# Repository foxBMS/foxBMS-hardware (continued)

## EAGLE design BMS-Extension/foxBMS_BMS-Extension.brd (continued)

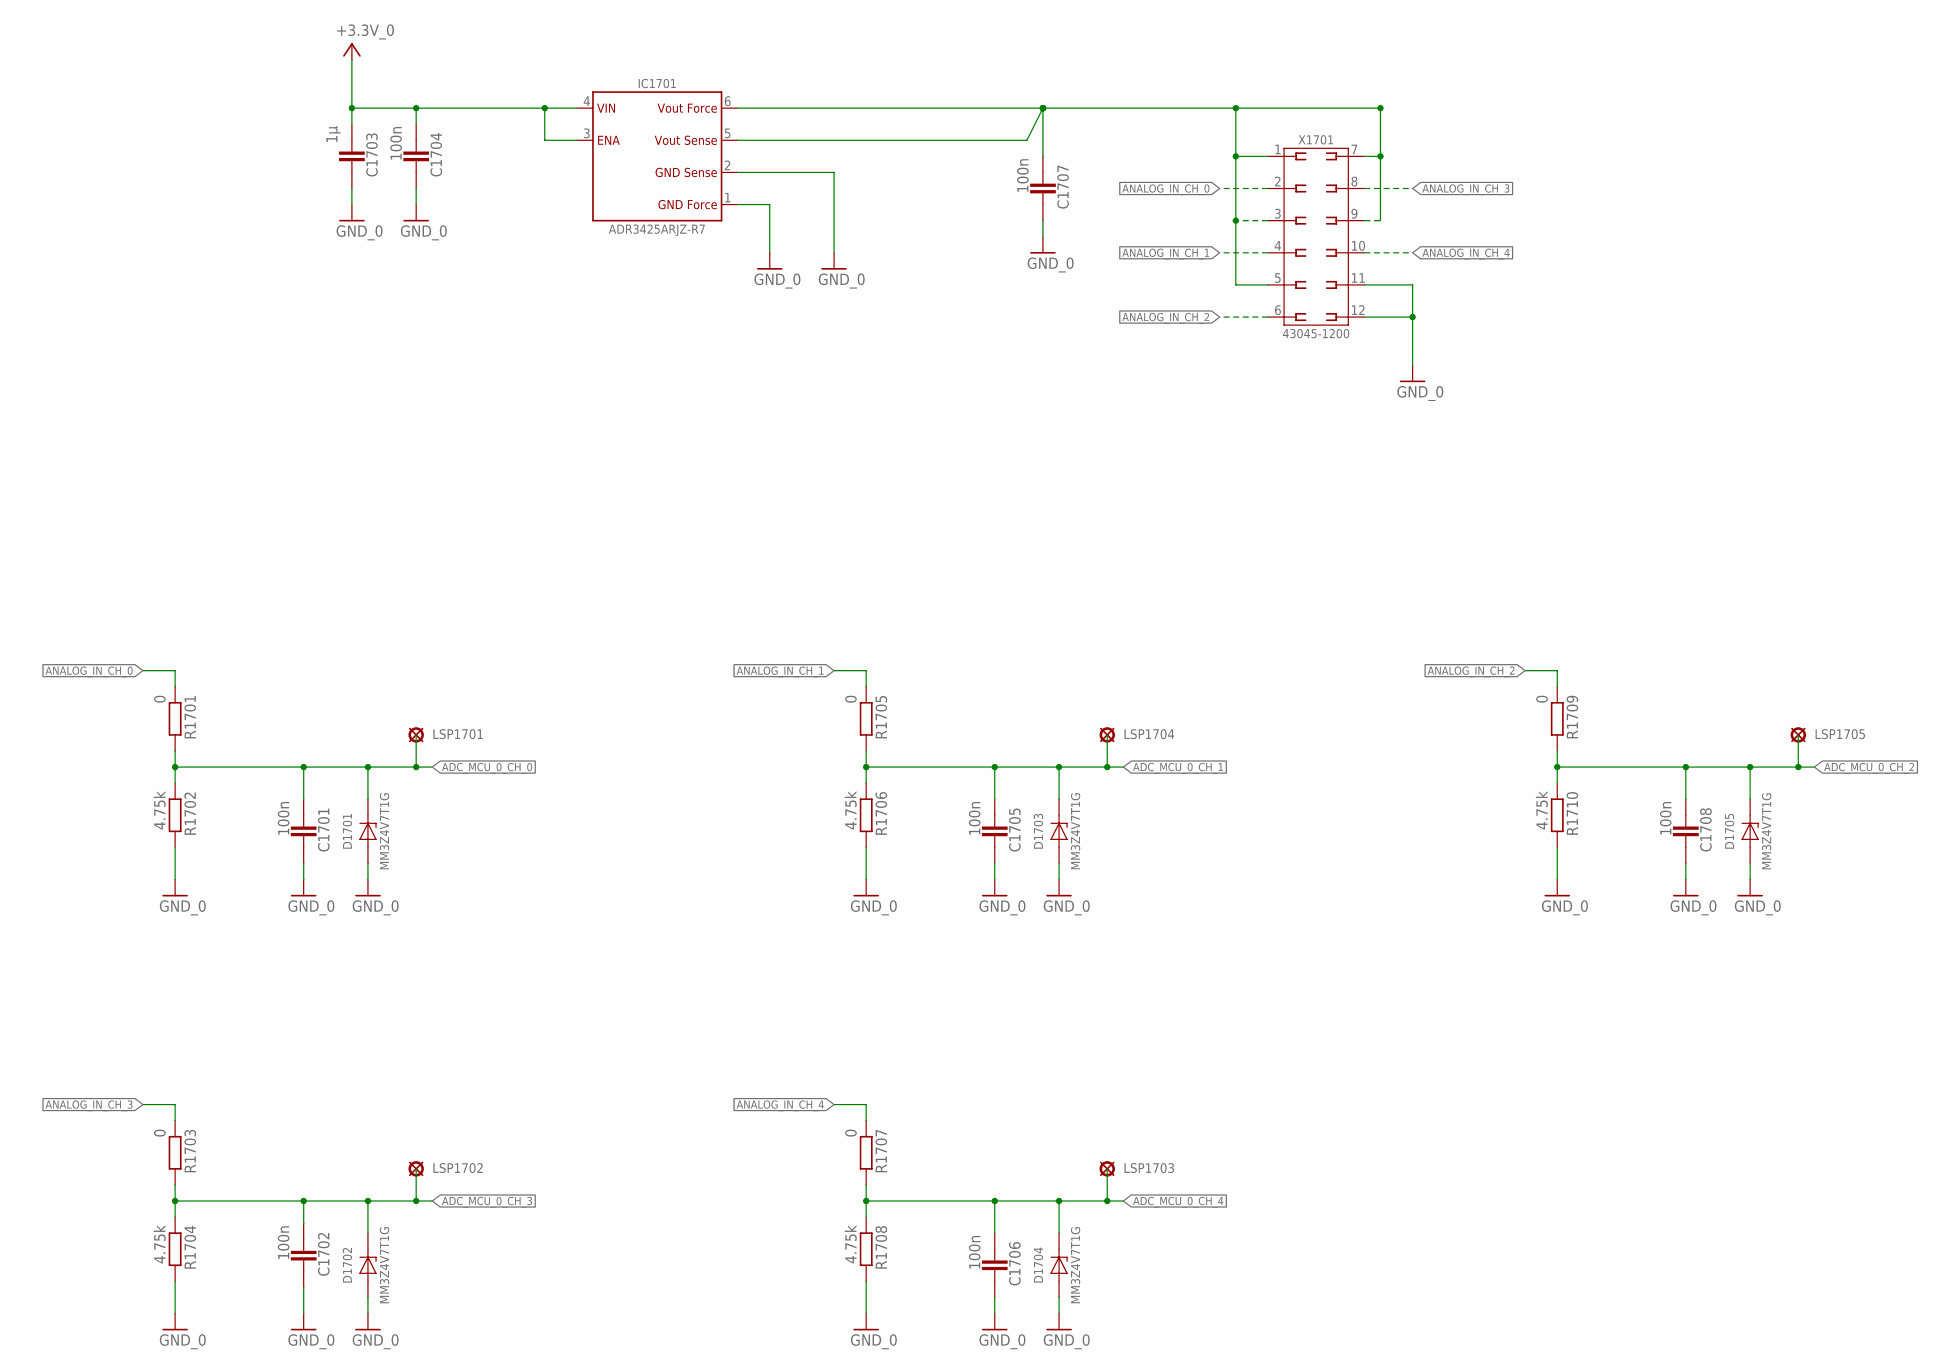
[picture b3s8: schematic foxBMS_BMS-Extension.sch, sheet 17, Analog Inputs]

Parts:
C1701, C1702, C1704, C1705, C1706, C1707, C1708: 100n; 0603
C1703: 1µ; 0603
D1701, D1702, D1703, D1704, D1705: MM3Z3V3ST1G; D_SMD_SOD323_(SC-76)_R_ON_REV01
IC1701: ADR3425ARJZ; IC_SMD_SOT23-6_(MO-178-AB)_R_AD_REV01
LSP1701, LSP1702, LSP1703, LSP1704, LSP1705: PAD_2.0X1.5MM; PAD2.0X1.5MM
R1701, R1703, R1705, R1707, R1709: 0; 0603
R1702, R1704, R1706, R1708, R1710: 4.75k; 0603
X1701: 43045-1200_MOLEX_12PIN; X_TH_MOLEX_43045-1200_R_REV01

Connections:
+3.3V_0: C1703.1, C1704.1, IC1701.3 (ENABLE), IC1701.4 (VIN); also elsewhere on the board
ADC_MCU_0_CH_0: C1701.1, D1701.C, LSP1701.P$1, R1701.2, R1702.1; also elsewhere on the board
ADC_MCU_0_CH_1: C1705.1, D1703.C, LSP1704.P$1, R1705.2, R1706.1; also elsewhere on the board
ADC_MCU_0_CH_2: C1708.1, D1705.C, LSP1705.P$1, R1709.2, R1710.1; also elsewhere on the board
ADC_MCU_0_CH_3: C1702.1, D1702.C, LSP1702.P$1, R1703.2, R1704.1; also elsewhere on the board
ADC_MCU_0_CH_4: C1706.1, D1704.C, LSP1703.P$1, R1707.2, R1708.1; also elsewhere on the board
ANALOG_IN_CH_0: R1701.1, X1701.2
ANALOG_IN_CH_1: R1705.1, X1701.4
ANALOG_IN_CH_2: R1709.1, X1701.6
ANALOG_IN_CH_3: R1703.1, X1701.8
ANALOG_IN_CH_4: R1707.1, X1701.10
GND_0: C1701.2, C1702.2, C1703.2, C1704.2, C1705.2, C1706.2, C1707.2, C1708.2, D1701.A, D1702.A, D1703.A, D1704.A, D1705.A, IC1701.1 (GND_FORCE), IC1701.2 (GND_SENSE), R1702.2, R1704.2, R1706.2, R1708.2, R1710.2, X1701.11, X1701.12; also elsewhere on the board
unnamed: C1707.1, IC1701.5 (VOUT_SENSE), IC1701.6 (VOUT_FORCE), X1701.1, X1701.3, X1701.5, X1701.7, X1701.9

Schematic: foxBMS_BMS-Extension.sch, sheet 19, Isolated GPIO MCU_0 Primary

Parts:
C1901, C1903, C1904, C1905, C1906, C1907: 100n; 0603
C1902: 1µ; 0603
D1901, D1902, D1903, D1904: CDSOD323-T05; D_SMD_SOD323_(SC-76)_R_BOURNS_REV01
IC1901: UA78L05ACPK; IC_SMD_SOT-89_(SC-62/TO-243)_(R-PSSO-F3)_R_TI_REV01
IC1902, IC1903: ADUM1402ARW; IC_SMD_SOIC-16_(JEDEC_MS-013-AA)_R_ANALOG_REV01
LSP1901, LSP1902, LSP1903, LSP1904, LSP1905, LSP1906, LSP1907, LSP1908: PAD_2.0X1.5MM; PAD2.0X1.5MM
R1901, R1902, R1905, R1906: 47; 0603
R1903, R1904, R1907, R1908: 10k; 0603
X1901: 43045-1000_MOLEX_10PIN; X_TH_MOLEX_43045-1000_R_REV01

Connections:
+3.3V_0: C1905.1, C1907.1, IC1902.10 (VE2), IC1902.16 (VDD2), IC1903.10 (VE2), IC1903.16 (VDD2); also elsewhere on the board
GND_0: C1905.2, C1907.2, IC1902.9 (GND2), IC1902.15 (GND2), IC1903.9 (GND2), IC1903.15 (GND2); also elsewhere on the board
GND_EXT_0: C1901.2, C1902.2, C1903.2, C1904.2, C1906.2, D1901.A, D1902.A, D1903.A, D1904.A, IC1901.2 (COM), IC1902.2 (GND1), IC1902.8 (GND1), IC1903.2 (GND1), IC1903.8 (GND1), R1903.1, R1904.1, R1907.1, R1908.1, X1901.9, X1901.10; also elsewhere on the board
ISO_GPIO_MCU_0_IN_0: IC1902.14 (VOA), LSP1903.P$1; also elsewhere on the board
ISO_GPIO_MCU_0_IN_0_EXT: R1901.2, X1901.5
ISO_GPIO_MCU_0_IN_1: IC1902.13 (VOB), LSP1901.P$1; also elsewhere on the board
ISO_GPIO_MCU_0_IN_1_EXT: R1902.2, X1901.6
ISO_GPIO_MCU_0_IN_2: IC1903.14 (VOA), LSP1905.P$1; also elsewhere on the board
ISO_GPIO_MCU_0_IN_2_EXT: R1905.2, X1901.7
ISO_GPIO_MCU_0_IN_3: IC1903.13 (VOB), LSP1907.P$1; also elsewhere on the board
ISO_GPIO_MCU_0_IN_3_EXT: R1906.2, X1901.8
ISO_GPIO_MCU_0_OUT_0: IC1902.12 (VIC), LSP1904.P$1; also elsewhere on the board
ISO_GPIO_MCU_0_OUT_0_EXT: IC1902.5 (VOC), R1903.2, X1901.1
ISO_GPIO_MCU_0_OUT_1: IC1902.11 (VID), LSP1902.P$1; also elsewhere on the board
ISO_GPIO_MCU_0_OUT_1_EXT: IC1902.6 (VOD), R1904.2, X1901.2
ISO_GPIO_MCU_0_OUT_2: IC1903.12 (VIC), LSP1906.P$1; also elsewhere on the board
ISO_GPIO_MCU_0_OUT_2_EXT: IC1903.5 (VOC), R1907.2, X1901.3
ISO_GPIO_MCU_0_OUT_3: IC1903.11 (VID), LSP1908.P$1; also elsewhere on the board
ISO_GPIO_MCU_0_OUT_3_EXT: IC1903.6 (VOD), R1908.2, X1901.4
ISO_GPIO_SUPPLY: C1903.1, C1904.1, C1906.1, IC1901.1 (OUT), IC1902.1 (VDD1), IC1902.7 (VE1), IC1903.1 (VDD1), IC1903.7 (VE1)
unnamed: D1903.C, IC1903.3 (VIA), R1905.1
unnamed: D1901.C, IC1902.3 (VIA), R1901.1
unnamed: D1902.C, IC1902.4 (VIB), R1902.1
unnamed: D1904.C, IC1903.4 (VIB), R1906.1
SUPPLY_EXT_0: C1901.1, C1902.1, IC1901.3 (IN); also elsewhere on the board

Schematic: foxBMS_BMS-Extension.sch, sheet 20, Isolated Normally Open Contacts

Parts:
D2001, D2002, D2003, D2004, D2005, D2006: DIODE-DO214BA; DO214BA
IC2001, IC2002, IC2003, IC2004, IC2005, IC2006: AQV25G2S; SOP06
LSP2001, LSP2002, LSP2003, LSP2004, LSP2005, LSP2006: PAD_2.0X1.5MM; PAD2.0X1.5MM
R2001, R2002, R2007, R2008, R2013, R2014: 10; 0603
R2003, R2004, R2009, R2010, R2015, R2016: 10k; 0603
R2005, R2006, R2011, R2012, R2017, R2018: 430; 0603
T2001, T2002, T2003, T2004, T2005, T2006: IRLML0100TRPBF; V_SMD_SOT-23_(TO-236AB)_R_IR_REV01
X2001: 43045-1200_MOLEX_12PIN; X_TH_MOLEX_43045-1200_R_REV01

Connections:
+3.3V_0: IC2001.1 (A), IC2002.1 (A), IC2003.1 (A), IC2004.1 (A), IC2005.1 (A), IC2006.1 (A); also elsewhere on the board
GND_0: R2003.1, R2004.1, R2009.1, R2010.1, R2015.1, R2016.1, T2001.2 (S), T2002.2 (S), T2003.2 (S), T2004.2 (S), T2005.2 (S), T2006.2 (S); also elsewhere on the board
ISONOC_0_CONTROL: LSP2001.P$1, R2001.2; also elsewhere on the board
ISONOC_0_NEGATIVE: D2001.A, IC2001.5 (S), X2001.7
ISONOC_0_POSITIVE: D2001.C, IC2001.4 (D1), IC2001.6 (D2), X2001.1
ISONOC_1_CONTROL: LSP2003.P$1, R2007.2; also elsewhere on the board
ISONOC_1_NEGATIVE: D2003.A, IC2003.5 (S), X2001.8
ISONOC_1_POSITIVE: D2003.C, IC2003.4 (D1), IC2003.6 (D2), X2001.2
ISONOC_2_CONTROL: LSP2005.P$1, R2013.2; also elsewhere on the board
ISONOC_2_NEGATIVE: D2005.A, IC2005.5 (S), X2001.9
ISONOC_2_POSITIVE: D2005.C, IC2005.4 (D1), IC2005.6 (D2), X2001.3
ISONOC_3_CONTROL: LSP2002.P$1, R2002.2; also elsewhere on the board
ISONOC_3_NEGATIVE: D2002.A, IC2002.5 (S), X2001.10
ISONOC_3_POSITIVE: D2002.C, IC2002.4 (D1), IC2002.6 (D2), X2001.4
ISONOC_4_CONTROL: LSP2004.P$1, R2008.2; also elsewhere on the board
ISONOC_4_NEGATIVE: D2004.A, IC2004.5 (S), X2001.11
ISONOC_4_POSITIVE: D2004.C, IC2004.4 (D1), IC2004.6 (D2), X2001.5
ISONOC_5_CONTROL: LSP2006.P$1, R2014.2; also elsewhere on the board
ISONOC_5_NEGATIVE: D2006.A, IC2006.5 (S), X2001.12
ISONOC_5_POSITIVE: D2006.C, IC2006.4 (D1), IC2006.6 (D2), X2001.6
unnamed: R2005.1, T2001.3 (D)
unnamed: R2011.1, T2003.3 (D)
unnamed: IC2003.2 (K), R2011.2
unnamed: R2017.1, T2005.3 (D)
unnamed: IC2005.2 (K), R2017.2
unnamed: R2006.1, T2002.3 (D)
unnamed: IC2002.2 (K), R2006.2
unnamed: R2012.1, T2004.3 (D)
unnamed: IC2004.2 (K), R2012.2
unnamed: R2018.1, T2006.3 (D)
unnamed: IC2006.2 (K), R2018.2
unnamed: IC2001.2 (K), R2005.2
unnamed: R2001.1, R2003.2, T2001.1 (G)
unnamed: R2007.1, R2009.2, T2003.1 (G)
unnamed: R2013.1, R2015.2, T2005.1 (G)
unnamed: R2002.1, R2004.2, T2002.1 (G)
unnamed: R2008.1, R2010.2, T2004.1 (G)
unnamed: R2014.1, R2016.2, T2006.1 (G)

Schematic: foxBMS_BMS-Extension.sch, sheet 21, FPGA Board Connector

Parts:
LSP2101, LSP2102: PAD_2.0X1.5MM; PAD2.0X1.5MM
SV2101: MA04-2

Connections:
+3.3V_0: LSP2101.P$1, SV2101.1; also elsewhere on the board
+5.0V_0: SV2101.2
GND_0: LSP2102.P$1, SV2101.5, SV2101.6; also elsewhere on the board
MCU_TO_FPGA_INTERFACE_MCU_0_CS: SV2101.8
MCU_TO_FPGA_INTERFACE_MCU_0_MISO: SV2101.3
MCU_TO_FPGA_INTERFACE_MCU_0_MOSI: SV2101.7
MCU_TO_FPGA_INTERFACE_MCU_0_SCK: SV2101.4

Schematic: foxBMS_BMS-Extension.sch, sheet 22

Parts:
JP2201, JP2202: PINHD-2X12; 2X12

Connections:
+3.3V_0: JP2201.1, JP2201.3, JP2202.1, JP2202.3; also elsewhere on the board
ADC_MCU_0_CH_0: JP2202.8; also elsewhere on the board
ADC_MCU_0_CH_1: JP2202.7; also elsewhere on the board
ADC_MCU_0_CH_2: JP2202.6; also elsewhere on the board
ADC_MCU_0_CH_3: JP2202.5; also elsewhere on the board
ADC_MCU_0_CH_4: JP2202.9; also elsewhere on the board
CAN_1_RX: JP2201.6; also elsewhere on the board
CAN_1_TRANS_STANDBY_CONTROL: JP2201.5; also elsewhere on the board
CAN_1_TX: JP2201.7; also elsewhere on the board
CONTACTOR_6_CONTROL: JP2201.18; also elsewhere on the board
CONTACTOR_6_FEEDBACK: JP2201.17; also elsewhere on the board
CONTACTOR_7_CONTROL: JP2201.16; also elsewhere on the board
CONTACTOR_7_FEEDBACK: JP2201.15; also elsewhere on the board
CONTACTOR_8_CONTROL: JP2202.10; also elsewhere on the board
CONTACTOR_8_FEEDBACK: JP2202.11; also elsewhere on the board
DATA_STORAGE_SPI_MISO: JP2201.21; also elsewhere on the board
DATA_STORAGE_SPI_MOSI: JP2201.19; also elsewhere on the board
DATA_STORAGE_SPI_SCK: JP2201.20; also elsewhere on the board
DATA_STORAGE_SPI_SDCARD_NSS: JP2201.23; also elsewhere on the board
GND_0: JP2201.2, JP2201.4, JP2202.2, JP2202.4; also elsewhere on the board
ISONOC_0_CONTROL: JP2202.16; also elsewhere on the board
ISONOC_1_CONTROL: JP2202.17; also elsewhere on the board
ISONOC_2_CONTROL: JP2202.18; also elsewhere on the board
ISONOC_3_CONTROL: JP2202.19; also elsewhere on the board
ISONOC_4_CONTROL: JP2202.20; also elsewhere on the board
ISONOC_5_CONTROL: JP2202.21; also elsewhere on the board
ISO_GPIO_MCU_0_IN_0: JP2202.22; also elsewhere on the board
ISO_GPIO_MCU_0_IN_1: JP2202.23; also elsewhere on the board
ISO_GPIO_MCU_0_IN_2: JP2201.13; also elsewhere on the board
ISO_GPIO_MCU_0_IN_3: JP2201.10; also elsewhere on the board
ISO_GPIO_MCU_0_OUT_0: JP2201.9; also elsewhere on the board
ISO_GPIO_MCU_0_OUT_1: JP2201.14; also elsewhere on the board
ISO_GPIO_MCU_0_OUT_2: JP2201.11; also elsewhere on the board
ISO_GPIO_MCU_0_OUT_3: JP2201.12; also elsewhere on the board
RS485_MCU_0_DE: JP2202.15; also elsewhere on the board
RS485_MCU_0_NRE: JP2202.14; also elsewhere on the board
RS485_MCU_0_RX: JP2202.13; also elsewhere on the board
RS485_MCU_0_TX: JP2202.12; also elsewhere on the board
SDCARD_SUPPLY_CONTROL: JP2201.22; also elsewhere on the board

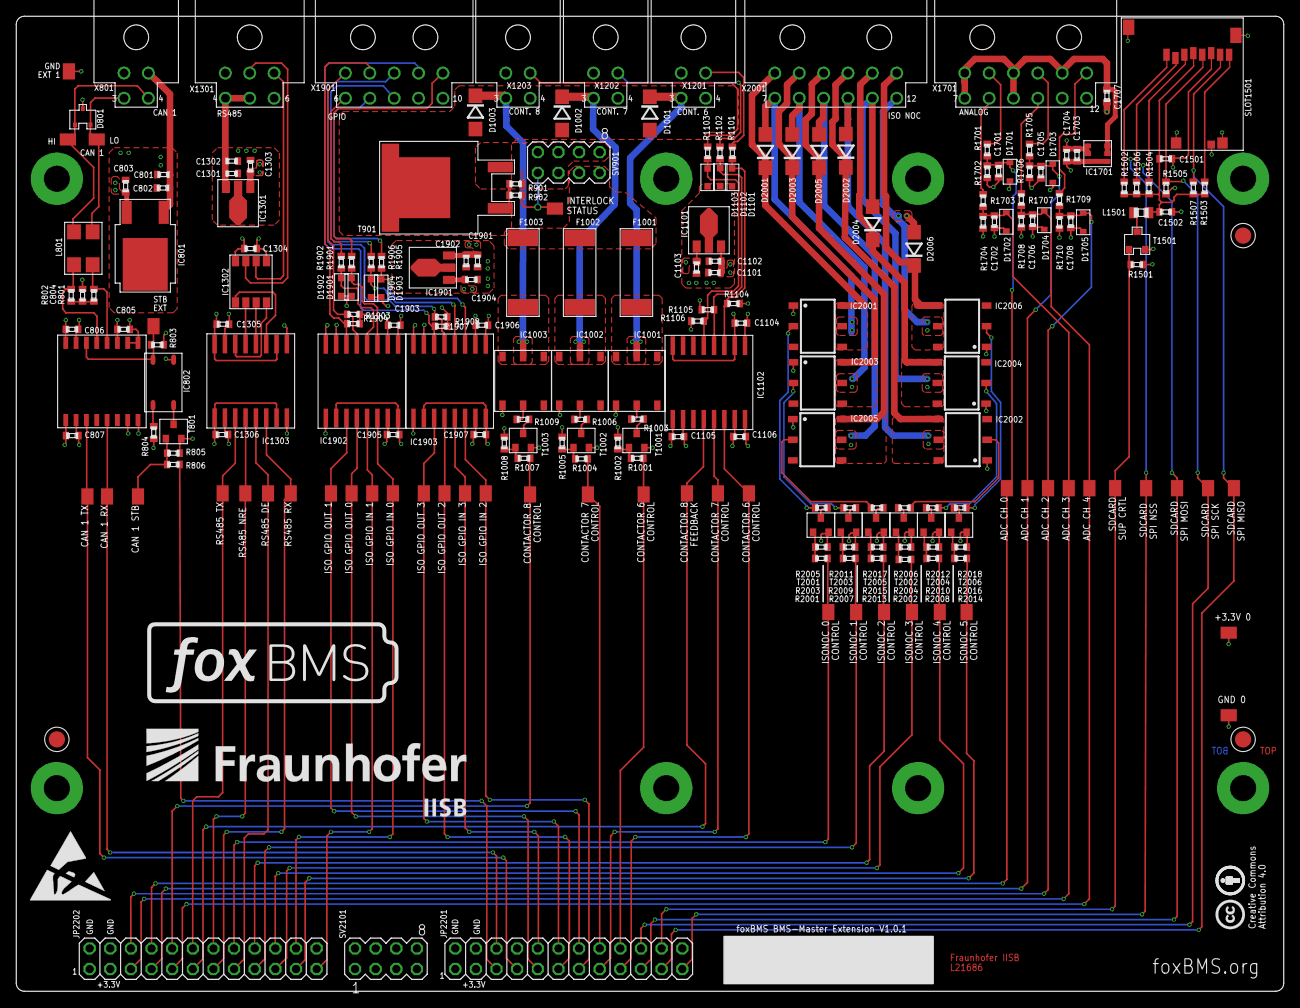
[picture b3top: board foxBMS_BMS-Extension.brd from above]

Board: 4 copper layers, 156.0 x 120.0 mm, 223 parts (0 on the bottom side), 141 nets.

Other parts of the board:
U$1: ESD_10.00
U$2, U$3, U$4: FIDUCIAL_1MM

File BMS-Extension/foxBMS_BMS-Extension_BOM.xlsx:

Populate | Qty | Value | Device | Package | Parts | Description | Farnell | Digikey | Mouser
 | Resistor
yes | 5 | 0 | R_MET_0603 | 0603 | R1701 R1703 R1705 R1707 R1709 | Resistor | 2059527
yes | 11 | 10 | R_MET_0603 | 0603 | R902 R1001 R1004 R1007 R2001 R2002 R2007 R2008 R2013 R2014 R806 | Resistor | 2302958
yes | 25 | 10k | R_MET_0603 | 0603 | R901 R1002 R1005 R1008 R1104 R1105 R1106 R1502 R1503 R1504 R1505 R1506 R1507 R1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 | Resistor | 2303192
yes | 5 | 4.75k | R_MET_0603 | 0603 | R1702 R1704 R1706 R1708 R1710 | Resistor | 2094611
yes | 10 | 430 | R_MET_0603 | 0603 | R1003 R1006 R1009 R2005 R2006 R2011 R2012 R2017 R2018 R804 | Resistor | 2145386
yes | 1 | 47k | R_MET_0603 | 0603 | R1501 | Resistor | 2303213
yes | 7 | 47 | R_MET_0603 | 0603 | R1101 R1102 R1103 R1901 R1902 R1905 R1906 | Resistor | 2145397
yes | 2 | 62 | R_MET_0603 | 0603 | R801 R802 | Resistor | 2303039
 | Capacitor
yes | 4 | 100n 50V | C_NP0_0603 | 0603 | C1901 C802 C1101 C1302 | Capacitor | 2346967
yes | 26 | 100n | C_X7R_0603 | 0603 | C803 C804 C805 C806 C807 C1103 C1104 C1105 C1106 C1303 C1304 C1305 C1306 C1701 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 | Capacitor | 1828890
yes | 3 | 1µ | C_X7R_0603 | 0603 | C1703 C1902 C1502 | Capacitor | 1907343
yes | 3 | 1µ 35V | C_X7R_0603 | 0603 | C801 C1102 C1301 | Capacitor | 2346909
 | Testpad
no | 44 | PAD_2.0X1.5MM | PAD_2.0X1.5MM | PAD2.0X1.5MM | LSP801 LSP802 LSP803 LSP804 LSP805 LSP806 LSP807 LSP901 LSP1001 LSP1002 LSP1003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 | Testpoint |  | 952-2664-1-ND
 | L
yes | 1 |  | B82789N | B82789*N | L801 |  |  |  | 871-B82789C513N2
yes | 1 | 22u | L1210 | L1210 | L1501 |  | 2443249
 | Diode
yes | 5 | MM3Z3V3ST1G | MM3Z_XVX_T1 | SOD323 | D1701 D1702 D1703 D1704 D1705 | MM3Z_xVx_T1 Series Zener Diode |  | MM3Z3V3ST1GOSCT-ND
yes | 7 | CDSOD323-T05 | CDSOD323-T05 | SOD323 | D1101 D1102 D1103 D1901 D1902 D1903 D1904 | TVS CDSOD323-T05 | 2341914
yes | 1 | PESD1CAN | PESD1CAN | SOT-23_NEU | D801 | NXP PESD1CAN CAN bus ESD protection diode | 1510703
no | 9 |  | DIODE-DO214BA | DO214BA | D1001 D1002 D1003 D2001 D2002 D2003 D2004 D2005 D2006 | DIODE | 1467477
 | Transistor
yes | 1 | BSS84P | BSS84P | SOT23 | T1501 | #2245 | 1056526
yes | 1 | BUK964R8-60E | BUK964R8-60E | TO-263AB | T901 | #2797 N-Channel PowerTrench MOSFET 60V, 75A 10.5mOhm | 2254205
yes | 10 | IRLML0100TRPBF | IRLML0100TRPBF | SOT-23 | T801 T1001 T1002 T1003 T2001 T2002 T2003 T2004 T2005 T2006 |  | 1783928
 | IC
yes | 1 | ADR3425ARJZ | ADR3425ARJZ | SOT23-6 | IC1701 | Micropower, high accuracy, voltage references | 2377039
yes | 1 | ADUM3300 | ADUM3300 | SO-16W | IC1102 | Triple-Channel Digital Isolators | 2409432
yes | 1 | ADUM3401 | ADUM3401 | SO16W | IC1303 | Analog Devices Magnetkoppler 4-Kanal | 1274129
yes | 2 | ADUM3402 | ADUM3402 | SO16W | IC1902 IC1903 | Analog Devices Magnetkoppler 4-Kanal | 1274127
yes | 1 | LT1785CS8#PBF | LT1785CS8#PBF | SOIC8 | IC1302 | Low Power RS485 Interface Transceiver | 1663498
yes | 1 | TJA1052IT/5Y | TJA1052IT/5Y | SO16W | IC803 |  | 2400552
 | Opto
yes | 9 | AQV252G2SX | AQV252G2SX | SOP06 | IC1001 IC1002 IC1003 IC2001 IC2002 IC2003 IC2004 IC2005 IC2006 |  |  | 255-3594-1-ND
yes | 1 | CPC1008N | CPC1008N | SOP4 | IC802 | CLARE - Single-Pol, Normally Open 4-Pin SOP OptoMOS Relay, 150mA load current | 1653755
 | Regulator
yes | 1 | KA7805ERT | KA7805ERT | TO252 | IC801 | Positive VOLTAGE REGULATOR | 2102585
yes | 3 | UA78L05CPK | UA78L05CPK | SOT89 | IC1101 IC1301 IC1901 | POSITOIV-VOLTAGE REGULATORS | 2112604
 | Misc
yes | 1 |  | 47352-1001 | 47352-1001 | SD-Micro SLOT |  | 2424133
yes | 3 | 630MA_UMT | 630MA_UMT | F_SMD_11,00MMX3,00MMX3,00MM_(UMT)_R_SCHURTER_REV01 | F1001 F1002 F1003 | UMT-Serie - Schurter Electronic Components |  | 486-2077-ND | 693-3403.0164.11
 | Connector THD
yes | 1 |  | HEADER_POS10_43045-1000 | 43045-1000 | X1901 | Molex - Micro-Fit 3.0 Series connector, 3.00mm (0.118) pitch header, 10 positio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 | 1012255
yes | 2 |  | HEADER_POS12_43045-1200 | 43045-1200 | X1701 X2001 | Molex - Micro-Fit 3.0 Series connector, 3.00mm (0.118) pitch header, 12 positio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 | 9732977
yes | 4 |  | HEADER_POS4_43045-0400 | 43045-0400 | X801 X1201 X1202 X1203 | Molex - Micro-Fit 3.0 Series connector, 3.00mm (0.118) pitch header, 4 position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 | 9733019
yes | 1 |  | HEADER_POS6_43045-0600 | 43045-0600 | X1301 | Molex - Micro-Fit 3.0 Series connector, 3.00mm (0.118) pitch header, 6 position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 | 1012252
yes | 1 |  | MA04-2 | MA04-2 | SV901 | PIN HEADER |  | SAM1096-04-ND
no | 1 |  |  |  | SV2101 |  | 2025250
yes | 2 |  | PINHD-2X12 | 2X12 | JP2201 JP2202 | PIN HEADER |  | SAM1096-12-ND

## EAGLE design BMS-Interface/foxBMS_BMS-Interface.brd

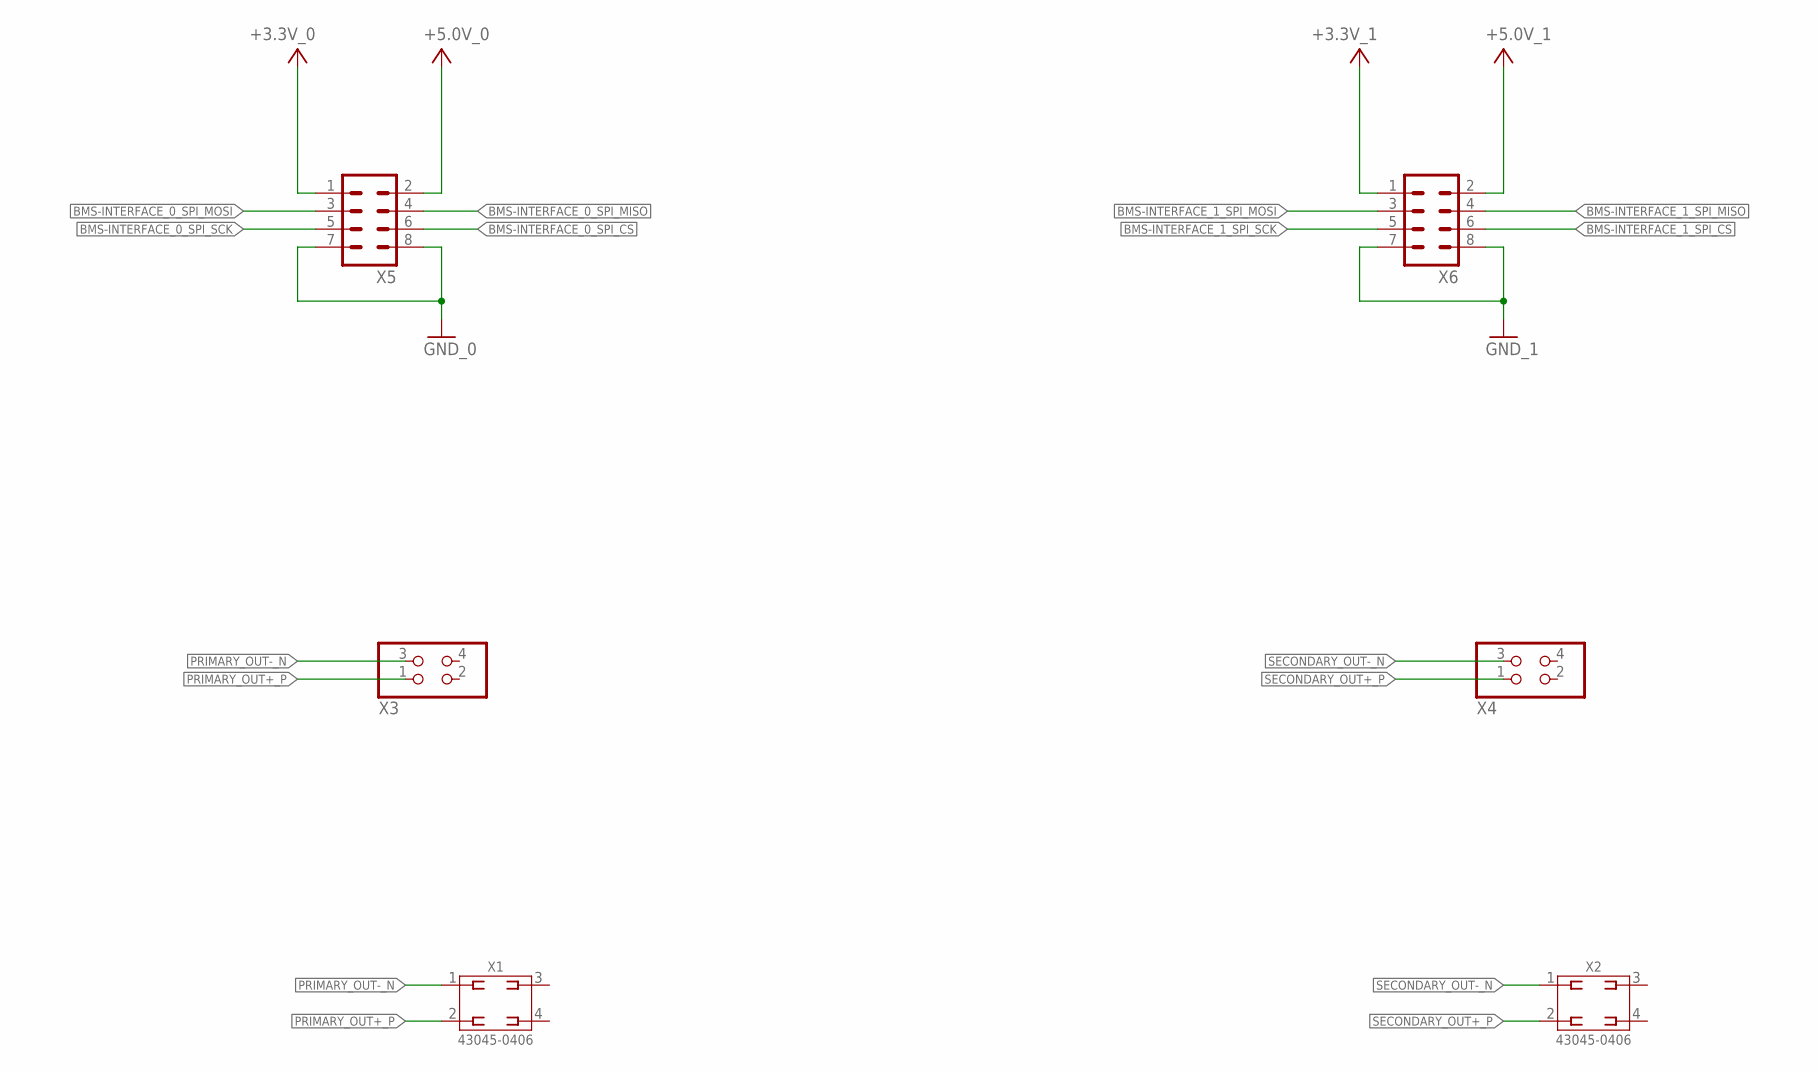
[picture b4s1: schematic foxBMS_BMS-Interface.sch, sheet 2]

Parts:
X1, X2: 43045-0406_MOLEX_4PIN; X_SMD_MOLEX_43045-0408_R_REV01
X3, X4: PINHD-2X2; 2X02
X5, X6: MA04-2

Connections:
+3.3V_0: X5.1; also elsewhere on the board
+3.3V_1: X6.1; also elsewhere on the board
+5.0V_0: X5.2
+5.0V_1: X6.2
BMS-INTERFACE_0_SPI_CS: X5.6; also elsewhere on the board
BMS-INTERFACE_0_SPI_MISO: X5.4; also elsewhere on the board
BMS-INTERFACE_0_SPI_MOSI: X5.3; also elsewhere on the board
BMS-INTERFACE_0_SPI_SCK: X5.5; also elsewhere on the board
BMS-INTERFACE_1_SPI_CS: X6.6; also elsewhere on the board
BMS-INTERFACE_1_SPI_MISO: X6.4; also elsewhere on the board
BMS-INTERFACE_1_SPI_MOSI: X6.3; also elsewhere on the board
BMS-INTERFACE_1_SPI_SCK: X6.5; also elsewhere on the board
GND_0: X5.7, X5.8; also elsewhere on the board
GND_1: X6.7, X6.8; also elsewhere on the board
PRIMARY_OUT+_P: X1.2, X3.1; also elsewhere on the board
PRIMARY_OUT-_N: X1.1, X3.3; also elsewhere on the board
SECONDARY_OUT+_P: X2.2, X4.1; also elsewhere on the board
SECONDARY_OUT-_N: X2.1, X4.3; also elsewhere on the board

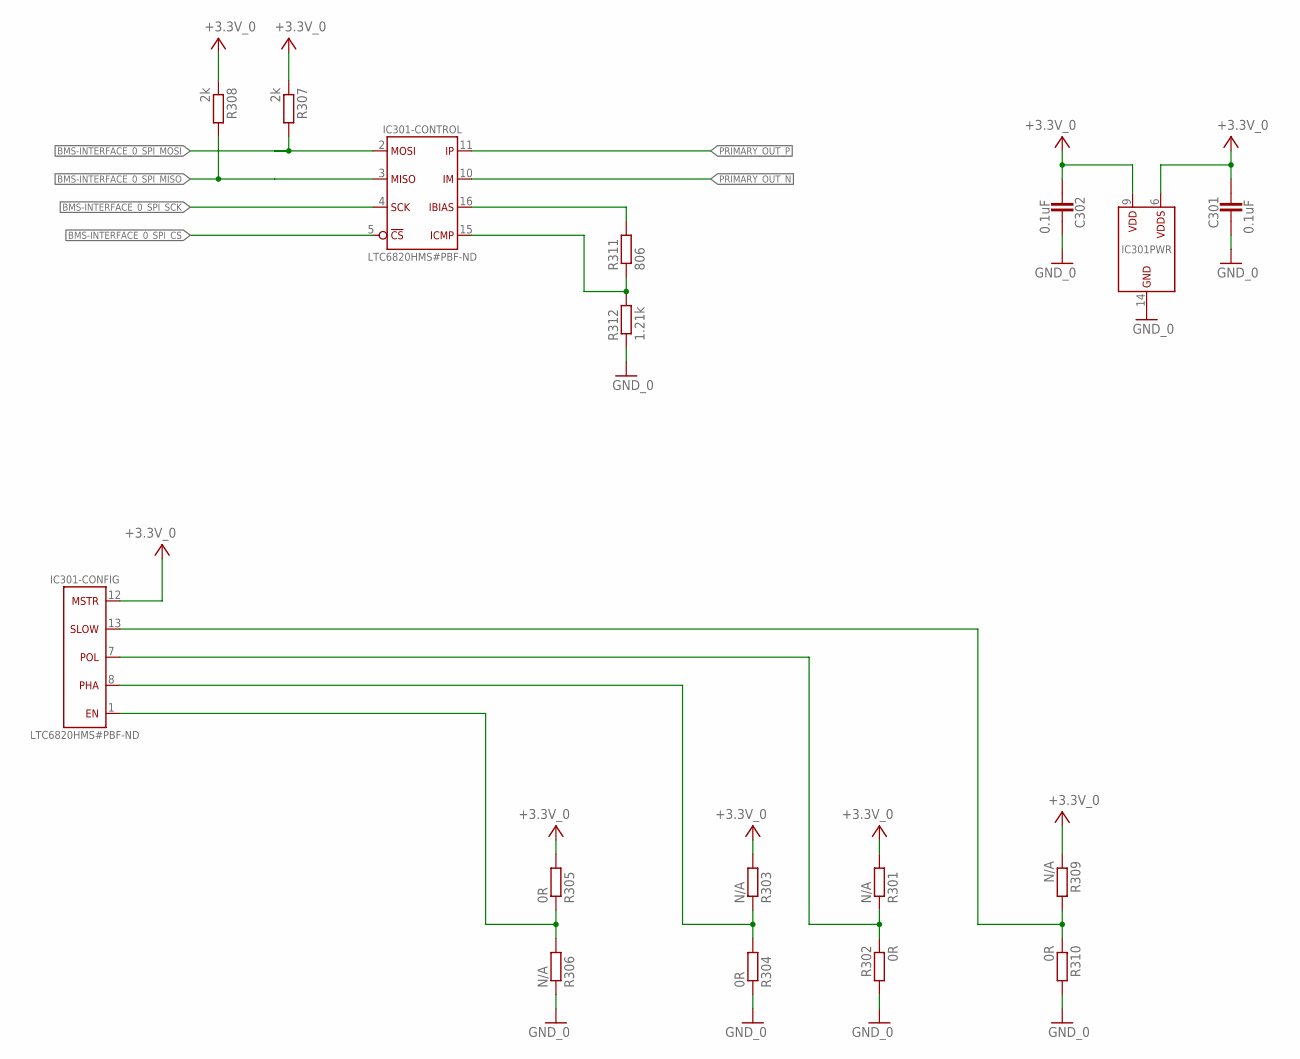
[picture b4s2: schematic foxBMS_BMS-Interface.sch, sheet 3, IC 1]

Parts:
C301, C302: 0.1uF; 0603
IC301: LTC6820HMS#PBF; IC_SMD_MSOP-16_(MS16)_R_LINEAR_REV01
R301, R303, R306, R309: N/A; 0603
R302, R304, R305, R310: 0R; 0603
R307, R308: 2k; 0603
R311: 806; 0603
R312: 1.21k; 0603

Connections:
+3.3V_0: C301.2, C302.2, IC301.6 (VDDS), IC301.9 (VDD), IC301.12 (MSTR), R301.2, R303.2, R305.2, R307.1, R308.1, R309.1; also elsewhere on the board
BMS-INTERFACE_0_SPI_CS: IC301.5 (!CS); also elsewhere on the board
BMS-INTERFACE_0_SPI_MISO: IC301.3 (MISO), R308.2; also elsewhere on the board
BMS-INTERFACE_0_SPI_MOSI: IC301.2 (MOSI), R307.2; also elsewhere on the board
BMS-INTERFACE_0_SPI_SCK: IC301.4 (SCK); also elsewhere on the board
EN-BACKUP: IC301.1 (EN), R305.1, R306.2
GND_0: C301.1, C302.1, IC301.14 (GND), R302.2, R304.1, R306.1, R310.2, R312.1; also elsewhere on the board
unnamed: IC301.16 (IBIAS), R311.2
unnamed: IC301.15 (ICMP), R311.1, R312.2
PHA-PRIMARY: IC301.8 (PHA), R303.1, R304.2
POL-PRIMARY: IC301.7 (POL), R301.1, R302.1
PRIMARY_OUT_N: IC301.10 (IM); also elsewhere on the board
PRIMARY_OUT_P: IC301.11 (IP); also elsewhere on the board
SLOW-PRIMARY: IC301.13 (SLOW), R309.2, R310.1

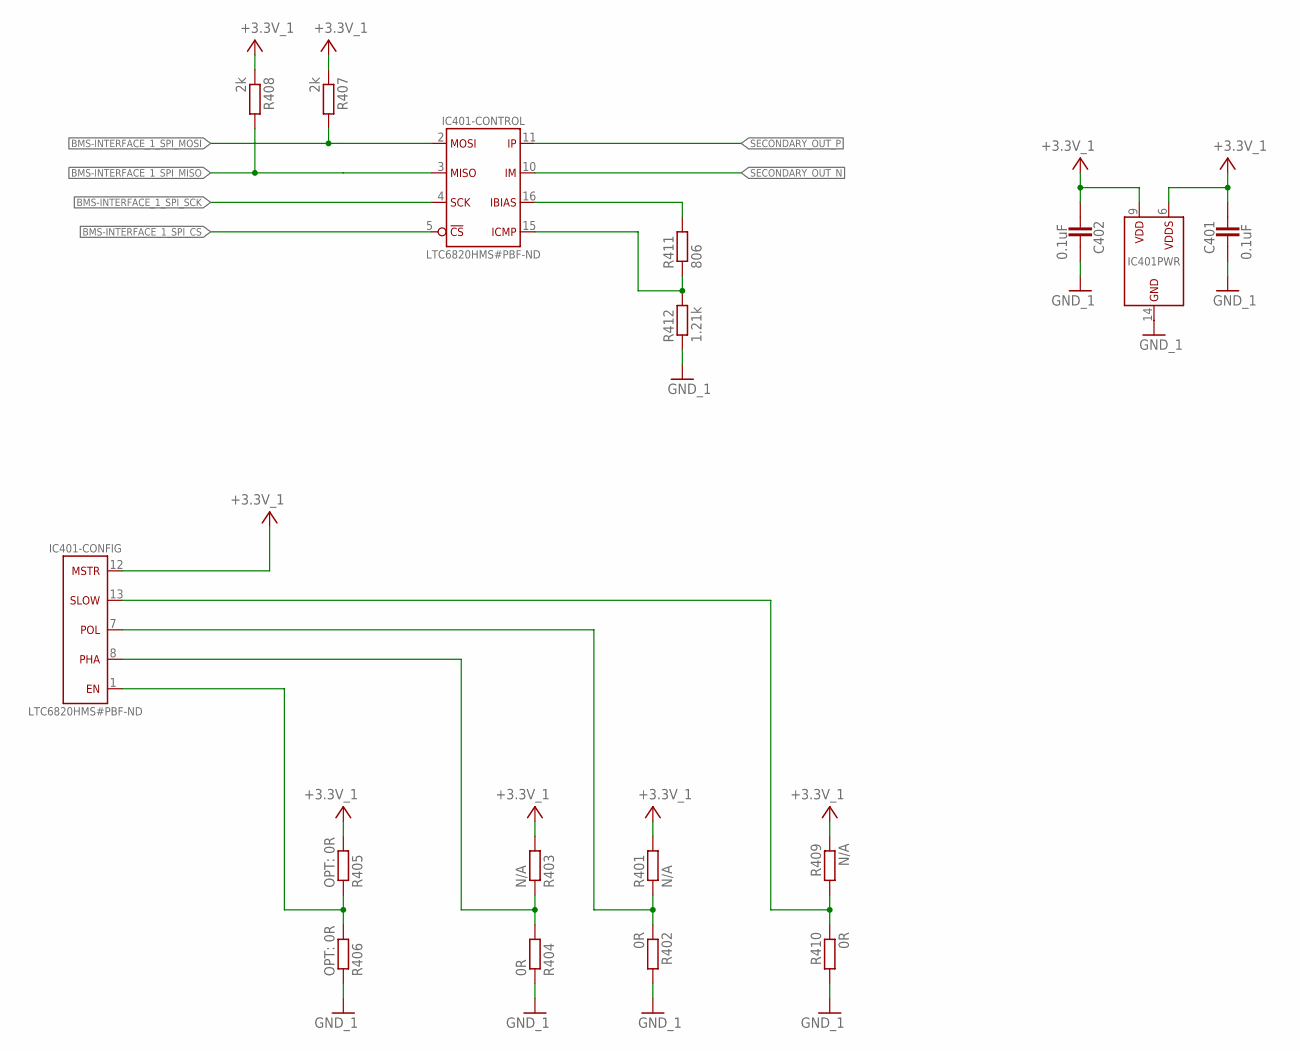
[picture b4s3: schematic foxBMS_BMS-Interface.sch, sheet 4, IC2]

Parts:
C401, C402: 0.1uF; 0603
IC401: LTC6820HMS#PBF; IC_SMD_MSOP-16_(MS16)_R_LINEAR_REV01
R401, R403, R409: N/A; 0603
R402, R404, R410: 0R; 0603
R405, R406: OPT: 0R; 0603
R407, R408: 2k; 0603
R411: 806; 0603
R412: 1.21k; 0603

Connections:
+3.3V_1: C401.2, C402.2, IC401.6 (VDDS), IC401.9 (VDD), IC401.12 (MSTR), R401.2, R403.2, R405.2, R407.1, R408.1, R409.1; also elsewhere on the board
BMS-INTERFACE_1_SPI_CS: IC401.5 (!CS); also elsewhere on the board
BMS-INTERFACE_1_SPI_MISO: IC401.3 (MISO), R408.2; also elsewhere on the board
BMS-INTERFACE_1_SPI_MOSI: IC401.2 (MOSI), R407.2; also elsewhere on the board
BMS-INTERFACE_1_SPI_SCK: IC401.4 (SCK); also elsewhere on the board
EN-BACKUP1: IC401.1 (EN), R405.1, R406.2
GND_1: C401.1, C402.1, IC401.14 (GND), R402.2, R404.1, R406.1, R410.2, R412.1; also elsewhere on the board
unnamed: IC401.15 (ICMP), R411.1, R412.2
unnamed: IC401.16 (IBIAS), R411.2
PHA-SECONDARY: IC401.8 (PHA), R403.1, R404.2
POL-SECONDARY: IC401.7 (POL), R401.1, R402.1
SECONDARY_OUT_N: IC401.10 (IM); also elsewhere on the board
SECONDARY_OUT_P: IC401.11 (IP); also elsewhere on the board
SLOW-SECONDARY: IC401.13 (SLOW), R409.2, R410.1

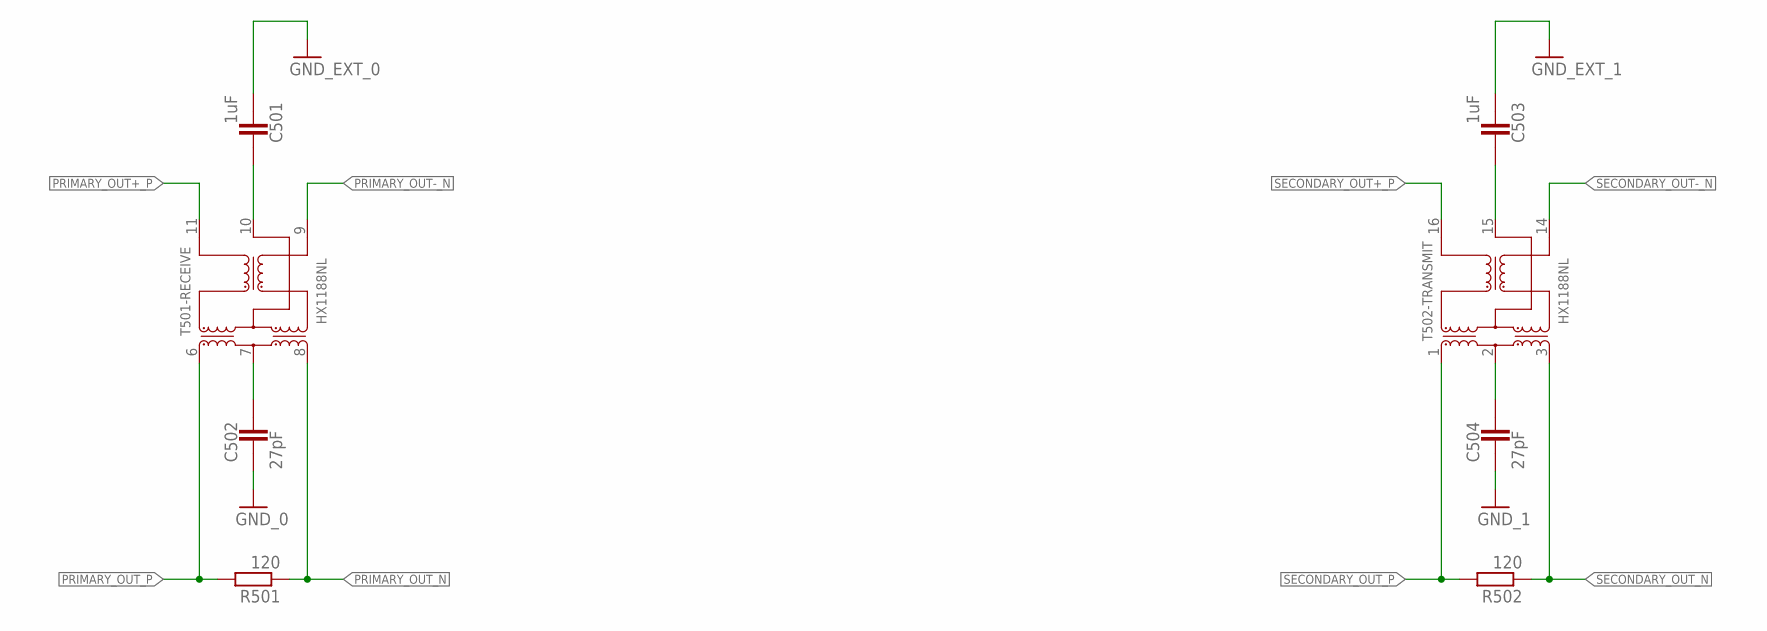
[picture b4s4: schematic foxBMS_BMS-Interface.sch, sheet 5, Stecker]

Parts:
C501, C503: 1uF; 0603
C502, C504: 27pF; 0603
R501, R502: 120; 0603
T501, T502: HX1188NL; TR_SMD_SOIC-16_(12,70MMX9,53MMX5,97MM)_R_PULSE_REV01

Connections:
GND_0: C502.1; also elsewhere on the board
GND_1: C504.1; also elsewhere on the board
unnamed 17: C502.2, T501.7 (CT); also elsewhere on the board
unnamed 23: C504.2, T502.2 (CT); also elsewhere on the board
unnamed: C501.2, T501.10 (CMT)
unnamed: C503.2, T502.15 (CMT)
PRIMARY_OUT_N: R501.1, T501.8 (D-); also elsewhere on the board
PRIMARY_OUT_P: R501.2, T501.6 (D+); also elsewhere on the board
SECONDARY_OUT_N: R502.1, T502.3 (D-); also elsewhere on the board
SECONDARY_OUT_P: R502.2, T502.1 (D+); also elsewhere on the board
